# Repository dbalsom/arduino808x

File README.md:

# ArduinoX86

### About ArduinoX86
I've written a blog article that gives an overview of this project and how it is used.

https://martypc.blogspot.com/2023/06/hardware-validating-emulator.html

This project was originally called Arduino8088, but then I expanded it to support the 8086, and then the 80186, and have plans to support 80286, so it is now named the suitably generic ArduinoX86.

### Description

This project expands on the basic idea of controlling a CPU via a microcontroller's GPIO pins to clock the CPU and read and write control and data signals.
This can be used to validate an emulator's accuracy, but also as a general method of exploring the operation of a CPU's instructions and timings.
This project specifically targets early Intel and compatible CPUs, such as the 8088, 8086, NEC V20, V30, and specific variants of the the Intel 80186. Future support for the 80286 is planned.

Where it differs from existing Raspberry Pi-based projects is that it uses an Arduino DUE for the expanded number of GPIO pins available. The DUE has enough GPIO to operate 808X-compatible CPUs in Maximum mode. This enables several useful signals to be read such as the QS0 & QS1 processor instruction queue status lines, which give us more insight into the internal state of the CPU. We can also enable inputs such as READY, NMI, INTR, and TEST, so we can execute interrupts, NMIs, emulate wait states, and potentially even simulate FPU and DMA operations.

I have been using this project to validate the cycle-accuracy of my PC emulator, [MartyPC](https://github.com/dbalsom/martypc), and produce CPU test suites for emulators, covering the [8088](https://github.com/singleStepTests/8088/), [V20](https://github.com/SingleStepTests/v20) and [8086](https://github.com/singleStepTests/8086/) to date. 

This project has three main components:
  - The CPU server software, which runs on the Arduino, resets and initializes the CPU, loads the initial register state, then hands off control to the client, reading the final register state when complete.
  - The CPU client software, which runs on your computer and controls the CPU after the CPU server has set up initial register state as desired.
  - The CPU socket PCB HAT(s), which seat on top of the Arduino, and provide a physical interface between the CPU and GPIO lines.

The original Arduino8088 board utilized an Arduino MEGA, but this board is now considered deprecated for this project. As of the current release, an [Arduino DUE](https://store.arduino.cc/products/arduino-due) should be used instead. Although the DUE has 3v GPIO, the current board design is modified for 3V operation. Several models of the 80C88 tolerate 3V well despite being 5V parts, due to the low clock rate employed.

Support for the newer [Arduino GIGA](https://store.arduino.cc/products/giga-r1-wifi) is in development but not quite complete. Unfortunately it seems to have insufficient power supply on the 3V line compared to the DUE.

A PCB hat for the 80286 that supports level shifting between 5V and 3V is in the design phase.

### 8086 Support

Revision 1.1 of the Arduino8088 board supports the 8086 and NEC V30 by adding a connection for the 8086's BHE pin. 

### 80186 Support

The ArduinoX86 cpu_server sketch supports operation of a low-voltage 80186. See the BOM section below for compatible parts. 
There is no PCB for the 80186, you will need to use a breakout board and connect directly to the Arduino DUE's headers. See [Using an 80186](https://github.com/dbalsom/arduinoX86/wiki/Using-an-80186) for more information.

## Can the CPU be clocked fast enough with an Arduino?

In short, no. We are well past the published minimum cycle times when executing programs via a serial protocol, cycle by cycle. NMOS process chips will fail to function in strange ways when clocked below this threshold. The issue is "dynamic logic" - logic gates that lose their state if not refrehsed electrically within a frequent enough interval. To function with ArduinoX86 a CMOS process CPU with a fully static core should be employed. These chips can be clocked down to 0Hz and still function. A list of compatible CPUs is provided in the BOM below.

## Credits

Inspired by and borrows from the Pi8088 validator created by Andreas Jonsson as part of the VirtualXT project:

https://github.com/andreas-jonsson/virtualxt/tree/develop/tools/validator/pi8088

A very similar project is homebrew8088's Raspberry Pi Hat:

https://github.com/homebrew8088/pi86

## To use

If you are using an 8088, 8086, V20 or V30, and you don't want to order and build the PCB, connect the GPIO pins to the CPU on a breadboard as specified in the KiCad project schematic.

If you are using an 80186, see the [wiki](https://github.com/dbalsom/arduinoX86/wiki/Using-an-80186) for connection instructions.

The main ArduinoX86 sketch, cpu_server, operates a simple binary serial protocol to execute operations on the CPU and read and write data, status and control signals. This is designed for integration with an emulator or instruction test generator.

Additionally, there is a sketch, 'run_program', that will take any user-supplied register state and array of instruction bytes defined in the source code, execute it, and print cycle traces and final register state. This is useful for investigating the timing and operation of certain instructions without needing any external software integrations, however it is restricted in the number of memory reads or writes it can support, due to the limited RAM on the Arduino MEGA (8k!) 'run_program' does not currently support the DUE.

An example application for cpu_server is provided, written in Rust, in the /crates/exec_program directory. It demonstrates how to upload arbitrary code to the ArduinoX86 and display cycle traces. The client will emulate the entire address space and set up a basic IVT.

## PCB

KiCad project files for the PCB are supplied. 

Version 1.1 adds a connection for the 8086's BHE pin, which is used by the 8086/V30/80186/80286 to drive the upper half of the 16-bit data bus.

> [!WARNING]  
> Please read all the notes in the next section before ordering/assembling parts. Failure to heed warnings will cause damage to your Arduino.

> [!CAUTION]
> Depending on the CPU used and the presence of an 8288 support chip, you may exceed the rated 3V power supply of the Arduino DUE.
> If your Arduino immediately turns off or does not turn on at all, you are likely triggering the overcurrent protection.
> 
> You can cut off the 3V supply lead from the header socket and provide external power from the top of the HAT.
>
> DO NOT connect external power to the 3V header without cutting the pin to the Arduino! Feeding current back into 3V OUT can damage your Arduino.

# BOM
- A compatible CPU:
  - For 8088, I recommend a CMOS variant such as a Harris or Oki 80C88. CMOS versions of the 8088 and 8086 were made by a number of manufacturers; all of them should work.
  - For 8086, Intel directly produced an 80C86 which works, so you might as well use it. The Harris 80C86 has also been tested but has minor differences. 
  - The NEC V20 and V30 were CMOS process CPUs and work as well.
  - Some NMOS process CPUs may work - the AMD D8088 will work, but the AMD D8086-2 will not. The original Intel 8088 (C)1978 will not function properly.
  - For 80186, I recommend the Intel 80L186EB. See [Using an 80186](https://github.com/dbalsom/arduinoX86/wiki/Using-an-80186) for more information.

  - For 80286, a level-shifting HAT is required as no 3V 286 was produced. A CMOS variant such as the Harris 80C286 is required. The CPU should be a PLCC68 form factor.
    The 286 HAT is still in the design phase.

> [!TIP]
> Beware of counterfeits on eBay and other online vendors. A legitimate chip will not look shiny and new with perfect printing on it. At best, you may get a functional
> CPU that has been resurfaced and reprinted, but there's not telling what you're actualy testing. 

- Optional: If using an 8088 or 8086, you can socket an Intel 8288 or OKI 82C88 Bus Controller.
  A CMOS version it not necessarily required, but they use less power.
  
  The 8288 is easily emulated but its ALE output is used to drive the LED on the Arduino8088 HAT.
  Change the `EMULATE_8288` define to 0 if using a physical 8288.

- A set of Arduino stacking headers (also usable with DUE) 
https://www.amazon.com/Treedix-Stacking-Headers-Stackable-Compatible/dp/B08G4FGBPQ

- A DIP-40 and (optionally) DIP-20 socket
  - Optional but highly recommended: A ZIF socket such as [https://www.amazon.com/-/en/gp/product/B00B886OZI](https://www.amazon.com/-/en/gp/product/B00B886OZI)
    to avoid breaking pins on repeated insertions

- (2x) 0805 0.047uf bypass capacitors
  https://www.mouser.com/ProductDetail/80-C0805C473KARAUTO

- Optional: A 12mm, active buzzer with 7.6mm pin spacing. 

  - For DUE: A 3V piezoelectric, low power buzzer <= 6mA
    https://www.mouser.com/ProductDetail/Mallory-Sonalert/PK-11N40PQ?qs=SXHtpsd1MbZ%252B7jeUyAAOVA%3D%3D
    
  - For MEGA: Any 3-5V buzzer <= 30mA
 
> [!WARNING]  
> Only connect an electromagnetic buzzer if using an Arduino MEGA.  The DUE has much lower GPIO max current supply.

- (2x) 750Ohm resistors (for LEDs)
  https://www.mouser.com/ProductDetail/667-ERA-6AED751V

- (2x) Any 0805 ~2V LED of your choice with 1.8-1.9mA forward current
  - https://www.mouser.com/ProductDetail/604-APTD2012LCGCK (Green)
  - https://www.mouser.com/ProductDetail/604-APT2012LSECKJ4RV (Orange)
 
- RS232 board for debug output - choose gender based on your desired cabling
  - https://www.amazon.com/Ultra-Compact-RS232-Converter-1Mbps/dp/B074BMLM11 (male)
  - https://www.amazon.com/Ultra-Compact-RS232-Converter-Female/dp/B074BTGLJN (female)
    
> [!WARNING]  
> DO NOT connect 5V to the RS232 board on the Arduino DUE. You will feed 5V into the RX GPIO pin and cause irreperable damage.

# Project Structure

## /asm

Assembly language files, intended to be assembled with NASM. To execute code on the ArduinoX86, one must supply two
binary files, one containing the program to be executed, and one containing the register values to load onto the CPU
before program execution. 

## /crates/ard808x_client

A library crate that implements a client for the ArduinoX86's serial protocol.

## /crates/ard808x_cpu

A library crate built on top of the `ard808x_client` crate, this provides a `RemoteCpu` struct that models CPU state 
and can execute programs.

## /crates/exec_program

A binary implementing an interface for the `ard808x_cpu` crate that will load a provided register state binary and 
execute the specified program binary.

## /pcb

Contains the KiCad project files and Gerber files for the Arduino8088 PCB.

## /sketches/cpu_server

The main Arduino sketch for ArduinoX86. Implements a server for a serial protocol enabling remote control of a 16-bit
Intel CPU on the Arduino DUE.

## /sketches/run_program

An older sketch that can execute a program directly on the Arduino MEGA. Supports the 8088 only.

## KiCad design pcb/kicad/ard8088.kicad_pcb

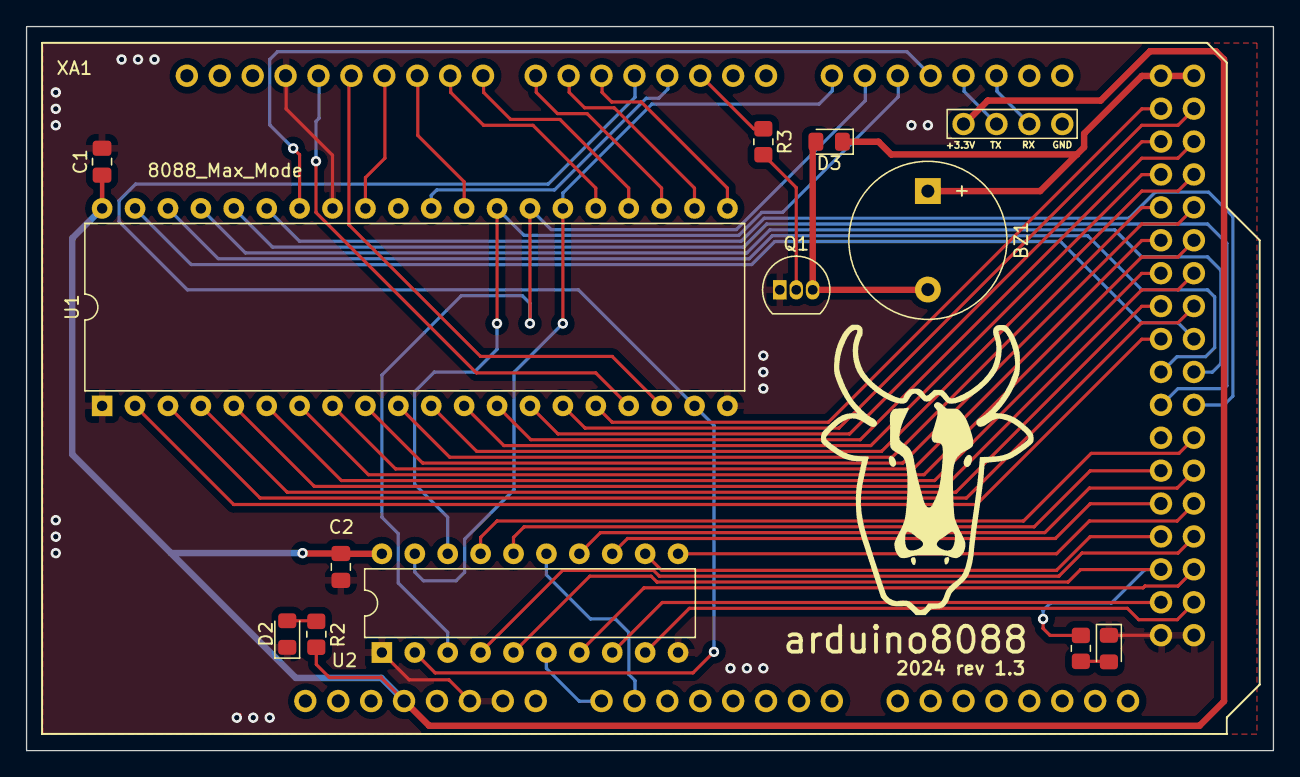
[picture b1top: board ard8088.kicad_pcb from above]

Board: 2 copper layers, 96.2 x 55.9 mm, 13 parts (0 on the bottom side), 58 nets.

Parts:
BZ1: Buzzer; Buzzer_12x9.5RM7.6
C1, C2: 0.1uf; C_0805_2012Metric_Pad1.18x1.45mm_HandSolder
D1, D2: LED; LED_0805_2012Metric_Pad1.15x1.40mm_HandSolder
D3: 1N4148; D_0805_2012Metric_Pad1.15x1.40mm_HandSolder
Q1: PN2222A; TO-92_Inline
R1: R1; R_0805_2012Metric_Pad1.20x1.40mm_HandSolder
R2, R3: R; R_0805_2012Metric_Pad1.20x1.40mm_HandSolder
U1: 8088_Max_Mode; DIP-40_W15.24mm
U2: 8288; DIP-20_W7.62mm
XA1: Arduino_Mega2560_Shield

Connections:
+3.3V: C1.1, C2.1, R2.1, U1.40 (VCC), U2.20 (VCC), XA1.3V3 (3.3V), XA1.S0
+5V: BZ1.1 (-), D3.1 (K), XA1.5V3 (5V), XA1.5V4 (5V)
/A8: U1.8 (A8), XA1.D30
/A9: U1.7 (A9), XA1.D31
/A10: U1.6 (A10), XA1.D32
/A11: U1.5 (A11), XA1.D33
/A12: U1.4 (A12), XA1.D34
/A13: U1.3 (A13), XA1.D35
/A14: U1.2 (A14), XA1.D36
/A15: U1.39 (A15), XA1.D37
/A16: U1.38 (A16/S3), XA1.D38
/A17: U1.37 (A17/S4), XA1.D39
/A18: U1.36 (A18/S5), XA1.D40
/A19: U1.35 (A19/S6), XA1.D41
/AD0: U1.16 (AD0), XA1.D22
/AD1: U1.15 (AD1), XA1.D23
/AD2: U1.14 (AD2), XA1.D24
/AD3: U1.13 (AD3), XA1.D25
/AD4: U1.12 (AD4), XA1.D26
/AD5: U1.11 (AD5), XA1.D27
/AD6: U1.10 (AD6), XA1.D28
/AD7: U1.9 (AD7), XA1.D29
/ALE: R1.1, U2.5 (ALE), XA1.D50
/CEN: U2.15 (CEN), XA1.A1
/CLK: U1.19 (CLK), U2.2 (CLK), XA1.D4
/DEN: U2.16 (DEN), XA1.D44
/DT/~R: U2.4 (DT/~R), XA1.D49
/INTR: U1.18 (INTR), XA1.D12
/MCE/~PDEN: U2.17 (MCE/~PDEN), XA1.D43
/NMI: U1.17 (NMI), XA1.D13
/QS1: U1.24 (QS1), XA1.D8
/QSO: U1.25 (QS0), XA1.D9
/READY: U1.22 (READY), XA1.D6
/RESET: U1.21 (RESET), XA1.D5
/S0: U1.26 (~S0), U2.19 (~S0), XA1.D14 (D14_TX3)
/S1: U1.27 (~S1), U2.3 (~S1), XA1.D15 (D15_RX3)
/S2: U1.28 (~S2), U2.18 (~S2), XA1.D16 (D16_TX2)
/ser0: XA1.D18 (D18_TX1), XA1.S1
/ser1: XA1.D19 (D19_RX1), XA1.S2
/~AEN: U2.6 (~AEN), XA1.A0
/~AIOWC: U2.12 (~AIOWC), XA1.D48
/~AMWC: U2.8 (~AMWC), XA1.D52
/~BHE: U1.34 (HIGH), XA1.D17 (D17_RX2)
/~INTA: U2.14 (~INTA), XA1.D45
/~IORC: U2.13 (~IORC), XA1.D46
/~IOWC: U2.11 (~IOWC), XA1.D47
/~LOCK: U1.29 (~LOCK), XA1.D10
/~MRDC: U2.7 (~MRDC), XA1.D51
/~MWTC: U2.9 (~MWTC), XA1.D53 (D53_SS)
/~RD: U1.32 (~RD), XA1.D11
/~RQ/~GT1: U1.30 (~RQ/~GT1), XA1.D3 (D3_INT1)
/~TEST: U1.23 (~TEST), XA1.D7
GND: C1.2, C2.2, D1.1 (K), D2.1 (K), Q1.1 (E), U1.1 (GND), U1.20 (GND), U1.33 (MN/~MX), U2.1 (IOB), U2.10 (GND), XA1.GND1 (GND), XA1.GND2 (GND), XA1.GND3 (GND), XA1.GND5 (GND), XA1.GND6 (GND), XA1.S3
unnamed: BZ1.2 (+), D3.2 (A), Q1.3 (C)
unnamed: D1.2 (A), R1.2
unnamed: D2.2 (A), R2.2
unnamed: Q1.2 (B), R3.2
unnamed: R3.1, XA1.D2 (D2_INT0)

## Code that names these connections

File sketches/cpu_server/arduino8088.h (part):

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#endif

// -------------------------- CPU Input pins ----------------------------------
#define BHE_PIN 17
#define READ_BHE_PIN READ_PIN_D17

#define READY_PIN 6
#define TEST_PIN 7
#define LOCK_PIN 10
#define INTR_PIN 12
#define NMI_PIN 13

// -------------------------- CPU Output pins ---------------------------------
#define RQ_PIN 3

// --------------------------8288 Control Inputs ------------------------------
#define AEN_PIN 54
#define CEN_PIN 55

// --------------------------8288 Control lines -------------------------------
#define ALE_PIN 50
#define DTR_PIN 49
#define MCEPDEN_PIN 43
#define DEN_PIN 44

// --------------------------8288 Command lines -------------------------------
#define MRDC_PIN 51
#define AMWC_PIN 52
#define MWTC_PIN 53
#define IORC_PIN 46
#define AIOWC_PIN 48
#define IOWC_PIN 47
#define INTA_PIN 45

// -------------------------- Macro definitions  ---------------------------------

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
#if EMULATE_8288
  // D50: PC13
  #define READ_ALE_PIN       (I8288.ale)
  // D51: PC12
  #define READ_MRDC_PIN      (!I8288.mrdc)
  // D52: PB21
  #define READ_AMWC_PIN      (!I8288.amwc)
  // D53: PB14
  #define READ_MWTC_PIN      (!I8288.mwtc)
  // D46: PC17
  #define READ_IORC_PIN      (!I8288.iorc)
  // D48: PC15
  #define READ_AIOWC_PIN     (!I8288.aiowc)
  // D47: PC16
  #define READ_IOWC_PIN      (!I8288.iowc)
  // D45: PC18
  #define READ_INTA_PIN      (!I8288.inta)
#else
  #if defined(__SAM3X8E__) // If Arduino DUE

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
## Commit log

2025-05-23 Refactor project
2025-05-24 Add EmuEnter state
2025-05-26 Move 8080 emulation support to server
2025-05-26 add cycle_get_cycle_state
2025-05-26 add copy+clone to more enums
2025-06-08 initial 80186 support
2025-06-09 refactor to new NMI program termination method

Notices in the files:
sketches/cpu_server/arduino8088.h:
Arduino8088 Copyright 2022-2025 Daniel Balsom
